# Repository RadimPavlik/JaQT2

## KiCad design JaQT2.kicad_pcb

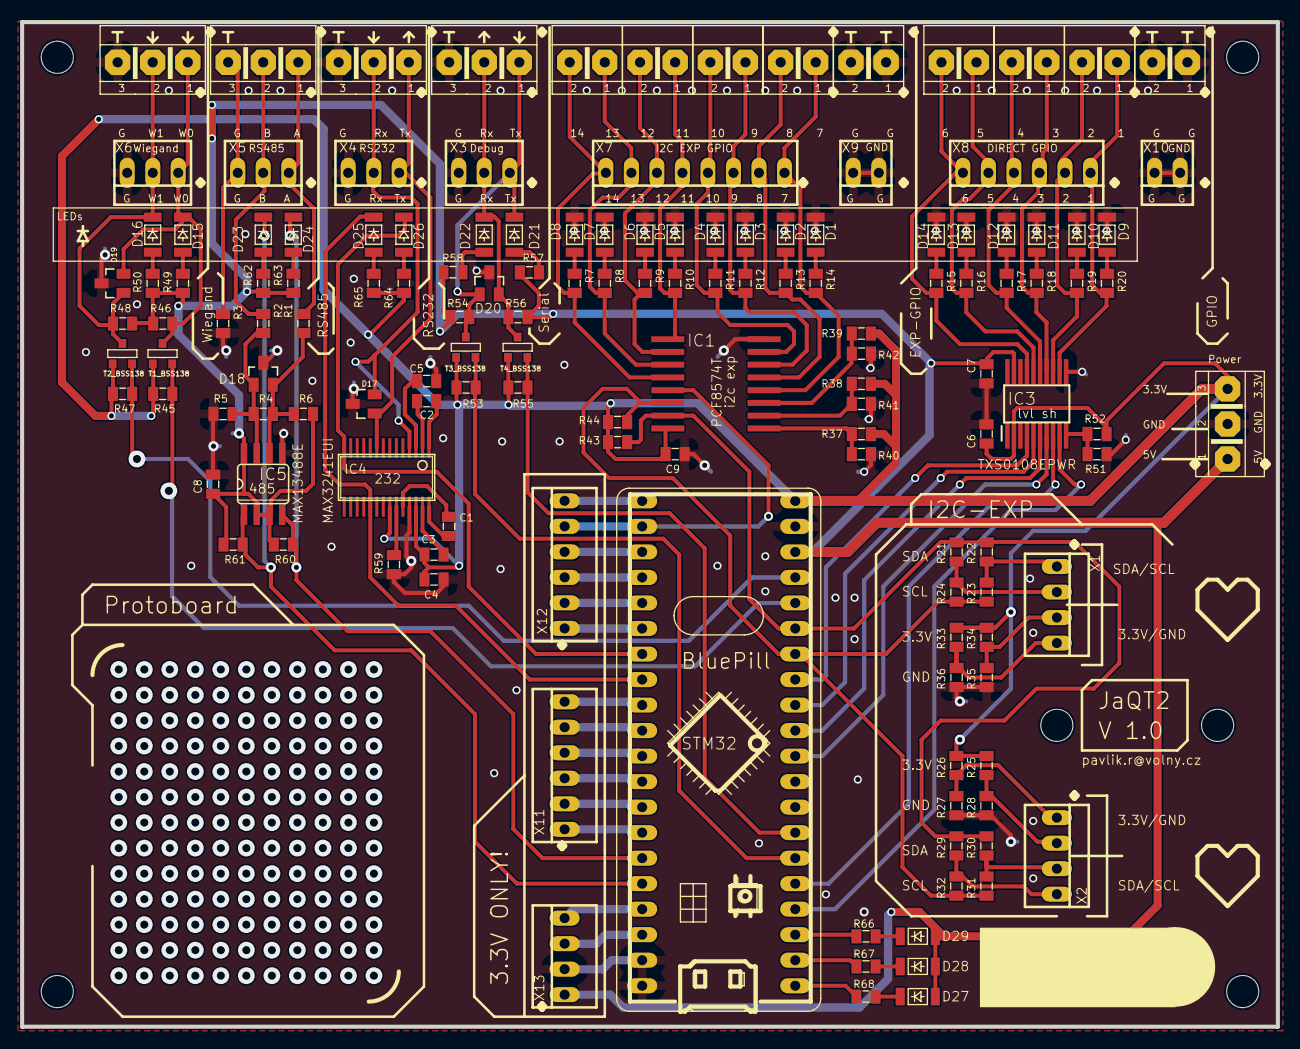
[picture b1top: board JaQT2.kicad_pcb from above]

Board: 2 copper layers, 125.0 x 100.0 mm, 148 parts (0 on the bottom side), 104 nets.

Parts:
@HOLE0, @HOLE1, @HOLE2, @HOLE3, @HOLE4, @HOLE5: (no value)
C1, C2, C3, C4, C5, C6, C7, C8, C9: 100nF; 0805
D1, D2, D3, D4, D5, D6, D7, D8, D9, D10, D11, D12, D13, D14, D15, D16, D21, D22, D23, D24, D25, D26, D27, D28, D29: P1206
D17: PESD15VL2BT,215; SOT23
D18: PESD12VL2BT,215; SOT23
D19, D20: PESD5V0L2UU; SOT23
IC1: PCF8574T; SO16W
IC3: TXS0108EPWR; SOP65P640X120-20N
IC4: MAX3241EUI; TSSOP28
IC5: MAX13488E; SO08
K1, K2, K3, K4, K12: ARK550/3; ARK550_3
K5, K6, K7, K8, K9, K10, K11, K13, K14: ARK550/2; ARK550_2
R1, R2, R3: 10; 0805
R4: 120_optional; 0805
R5, R6, R45, R46, R47, R48, R53, R54, R55, R56, R60, R61: 10k; 0805
R7, R8, R9, R10, R11, R12, R13, R14, R15, R16, R17, R18, R19, R20, R49, R50, R57, R58, R62, R63, R64, R65, R66, R67, R68: 100; 0805
R21, R22, R23, R24, R25, R26, R27, R28, R29, R30, R31, R32, R33, R34, R35, R36, R37, R38, R39, R40, R41, R42, R52, R59: 0; 0805
R43, R44: 4k7; 0805
R51: ?; 0805
STM32F103C8T6: BLUE_PILL
T1_BSS138, T2_BSS138, T3_BSS138, T4_BSS138: BSS138; SOT23
X1, X2, X13: 22-23-2041
X3, X4, X5, X6: 22-23-2031
X7: 22-23-2081
X8, X11, X12: 22-23-2061
X9, X10: 22-23-2021

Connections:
3.3V: C3.2, C4.2, C6.1, C9.1, IC1.16, IC3.2, IC4.22, IC4.26, K12.3, R25.2, R26.2, R33.2, R34.2, R37.2, R38.2, R39.2, R43.2, R44.2, R45.2, R47.2, R52.2, R53.2, R55.2, R64.2, R65.2, STM32F103C8T6.P$20, STM32F103C8T6.P$23, T1_BSS138.2, T2_BSS138.2, T3_BSS138.2, T4_BSS138.2, X13.3
5RX1: D20.2, D22.K, K1.2, R56.1, T4_BSS138.3, X3.2
5TX1: D20.1, D21.K, K1.1, R54.1, T3_BSS138.3, X3.1
5V: C7.1, C8.1, D27.A, D28.A, D29.A, IC3.19, IC5.2, IC5.3, IC5.8, K12.1, R6.2, R46.2, R48.2, R49.2, R50.2, R54.2, R56.2, R57.2, R58.2, R60.2, R61.2, R62.2, R63.2, STM32F103C8T6.P$18, X13.1
DIR1: IC3.9, STM32F103C8T6.P$4
DIR2: IC3.8, STM32F103C8T6.P$5
DIR3: IC3.7, STM32F103C8T6.P$10
DIR4: IC3.6, STM32F103C8T6.P$11
DIR5: IC3.5, STM32F103C8T6.P$12
DIR6: IC3.4, STM32F103C8T6.P$13
GND: C4.1, C5.2, C6.2, C7.2, C8.2, C9.2, D1.K, D2.K, D3.K, D4.K, D5.K, D6.K, D7.K, D8.K, D9.K, D10.K, D11.K, D12.K, D13.K, D14.K, D17.3, D18.3, D19.3, D20.3, IC1.8, IC3.11, IC4.25, IC5.5, K1.3, K2.3, K4.3, K12.2, K13.1, K13.2, K14.1, K14.2, R3.1, R5.1, R27.1, R28.1, R35.1, R36.1, R40.1, R41.1, R42.1, R51.1, R59.1, STM32F103C8T6.P$19, STM32F103C8T6.P$21, STM32F103C8T6.P$22, X3.3, X4.3, X6.3, X9.1, X9.2, X10.1, X10.2, X13.2
unnamed: R22.1, R23.2, X1.1
unnamed: R21.1, R24.2, X1.2
unnamed: R34.1, R35.2, X1.3
unnamed: R33.1, R36.2, X1.4
unnamed: D28.K, R67.2
unnamed: R25.1, R28.2, X2.2
unnamed: D17.1, IC4.9, K2.1, X4.1
unnamed: D17.2, IC4.4, K2.2, X4.2
unnamed: D21.A, R57.1
unnamed: C1.2, IC4.28
unnamed: C1.1, IC4.24
unnamed: C2.2, IC4.1
unnamed: C2.1, IC4.2
unnamed: C3.1, IC4.27
unnamed: D23.A, R62.1
unnamed: D24.A, R63.1
unnamed: D27.K, R68.2
unnamed: D25.A, R65.1
unnamed: C5.1, IC4.3
unnamed: D26.A, R64.1
unnamed: R30.1, R31.2, X2.3
unnamed: R29.1, R32.2, X2.4
unnamed: D29.K, R66.2
unnamed: D15.A, R49.1
unnamed: D16.A, R50.1
unnamed: D22.A, R58.1
unnamed: K3.1, R1.2, X5.1
unnamed: K3.2, R2.2, X5.2
unnamed: K3.3, R3.2, X5.3
unnamed: IC4.23, R59.2
unnamed: D18.2, IC5.6, R1.1, R4.2, R6.1
unnamed: D18.1, IC5.7, R2.1, R4.1, R5.2
unnamed: IC1.1, R37.1, R40.2
unnamed: D16.K, D19.1, K4.2, R48.1, T2_BSS138.3, X6.2
unnamed: D15.K, D19.2, K4.1, R46.1, T1_BSS138.3, X6.1
unnamed: IC3.12, K9.1, R20.2, X8.1
unnamed: IC3.10, R51.2, R52.1
unnamed: IC1.4, K5.1, R14.2, X7.1
unnamed: IC1.5, K5.2, R13.2, X7.2
unnamed: IC1.6, K6.1, R12.2, X7.3
unnamed: IC1.7, K6.2, R11.2, X7.4
unnamed: IC1.9, K7.1, R10.2, X7.5
unnamed: IC1.10, K7.2, R9.2, X7.6
unnamed: IC1.11, K8.1, R8.2, X7.7
unnamed: IC1.12, K8.2, R7.2, X7.8
unnamed: D1.A, R14.1
unnamed: D2.A, R13.1
unnamed: D3.A, R12.1
unnamed: D4.A, R11.1
unnamed: D5.A, R10.1
unnamed: D6.A, R9.1
unnamed: D7.A, R8.1
unnamed: D8.A, R7.1
unnamed: D9.A, R20.1
unnamed: D10.A, R19.1
unnamed: D11.A, R18.1
unnamed: D12.A, R17.1
unnamed: D13.A, R16.1
unnamed: D14.A, R15.1
unnamed: IC1.2, R38.1, R41.2
unnamed: IC1.3, R39.1, R42.2
unnamed: R26.1, R27.2, X2.1
unnamed: IC3.13, K9.2, R19.2, X8.2
unnamed: IC3.14, K10.1, R18.2, X8.3
unnamed: IC3.15, K10.2, R17.2, X8.4
unnamed: IC3.16, K11.1, R16.2, X8.5
unnamed: IC3.17, K11.2, R15.2, X8.6
PA0: STM32F103C8T6.P$36, X12.2
PA1: STM32F103C8T6.P$35, X12.1
PA4: STM32F103C8T6.P$32, X11.6
PA5: STM32F103C8T6.P$31, X11.5
PA6: STM32F103C8T6.P$30, X11.4
PA7: STM32F103C8T6.P$29, X11.3
PB0: STM32F103C8T6.P$28, X11.2
PB1: STM32F103C8T6.P$27, X11.1
PB12: R68.1, STM32F103C8T6.P$1
PB13: R67.1, STM32F103C8T6.P$2
PB14: R66.1, STM32F103C8T6.P$3
PC13: IC1.13, STM32F103C8T6.P$39, X12.5
PC14: STM32F103C8T6.P$38, X12.4
PC15: STM32F103C8T6.P$37, X12.3
RESET: STM32F103C8T6.P$24, X13.4
RX1: R55.1, STM32F103C8T6.P$7, T4_BSS138.1
RX2: D25.K, IC4.19, STM32F103C8T6.P$33
RX3: D23.K, IC5.1, R61.1, STM32F103C8T6.P$25
SCL1: IC1.14, R23.1, R24.1, R31.1, R32.1, R44.1, STM32F103C8T6.P$14
SDA1: IC1.15, R21.2, R22.2, R29.2, R30.2, R43.1, STM32F103C8T6.P$15
TX1: R53.1, STM32F103C8T6.P$6, T3_BSS138.1
TX2: D26.K, IC4.14, STM32F103C8T6.P$34
TX3: D24.K, IC5.4, R60.1, STM32F103C8T6.P$26
VBAT: STM32F103C8T6.P$40, X12.6
W0: R45.1, STM32F103C8T6.P$16, T1_BSS138.1
W1: R47.1, STM32F103C8T6.P$17, T2_BSS138.1

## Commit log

2022-05-07 Initial import for converted project data
    - might include some problems regarding compatibility
